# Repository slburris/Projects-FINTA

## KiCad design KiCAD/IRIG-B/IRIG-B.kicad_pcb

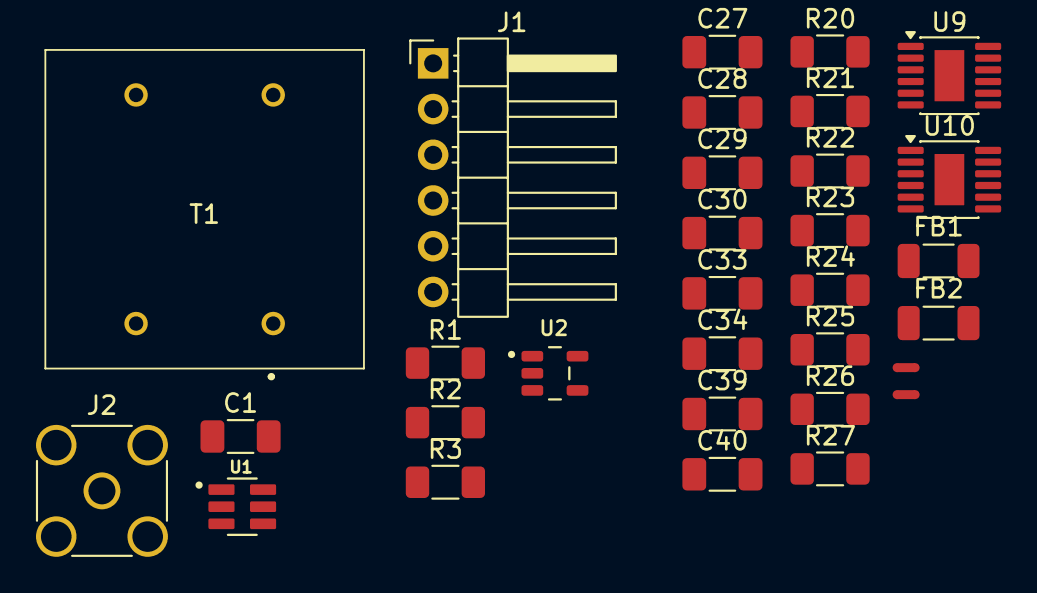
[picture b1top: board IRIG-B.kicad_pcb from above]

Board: 2 copper layers, 31 parts (0 on the bottom side), 26 nets, no tracks yet.

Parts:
C1, C27, C28, C30, C33, C34, C40: 10uf; C_1206_3216Metric_Pad1.33x1.80mm_HandSolder
C29, C39: 4.7uf; C_1206_3216Metric_Pad1.33x1.80mm_HandSolder
FB1, FB2: BLM31PG601; L_1206_3216Metric_Pad1.22x1.90mm_HandSolder
J1: Conn_01x06; PinHeader_1x06_P2.54mm_Horizontal
J2: Conn_Coaxial_Small; SMA_Amphenol_132291-12_Vertical
NT1, NT2: NetTie_2; NetTie-2_SMD_Pad0.5mm
R1: 1.4K; R_1206_3216Metric_Pad1.30x1.75mm_HandSolder
R2, R23: 1K; R_1206_3216Metric_Pad1.30x1.75mm_HandSolder
R3: 600; R_1206_3216Metric_Pad1.30x1.75mm_HandSolder
R20: 150K 0.1% 50ppm; R_1206_3216Metric_Pad1.30x1.75mm_HandSolder
R21, R25: 10K; R_1206_3216Metric_Pad1.30x1.75mm_HandSolder
R22: 113K; R_1206_3216Metric_Pad1.30x1.75mm_HandSolder
R24: 31.6K; R_1206_3216Metric_Pad1.30x1.75mm_HandSolder
R26: 50K 0.05% 5ppm; R_1206_3216Metric_Pad1.30x1.75mm_HandSolder
R27: 3K; R_1206_3216Metric_Pad1.30x1.75mm_HandSolder
T1: LM-NP-1001-B1L; LMNP1001B1L
U1: DAC121S101CIMKX_NOPB; SOT95P280X110-6N
U2: OPA171AIDBVR; SOT95P280X145-5NOPA171
U9, U10: LT3045xMSE; MSOP-12-1EP_3x4.039mm_P0.65mm_EP1.651x2.845mm

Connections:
+5VA: C40.1, NT2.2, U1.3 (VA), U9.11 (OUT), U9.12 (OUT)
+6V: C33.1, FB2.1
+15VA: C28.1, NT1.2, U2.5, U10.11 (OUT), U10.12 (OUT)
+16V: C30.1, FB1.1
GND: J1.2, R2.2, T1.4, U1.2 (GND), U2.2
GNDA: C27.2, C28.2, C29.2, C30.2, C33.2, C34.2, C39.2, C40.2, R20.2, R21.2, R23.2, R25.2, R26.2, R27.2, U9.9 (GND), U9.13 (GND), U10.9 (GND), U10.13 (GND)
unnamed: C1.1, R1.2, U2.1
unnamed: C1.2, R3.1
unnamed: J1.3, U1.5 (SCLK)
unnamed: J1.5, U1.4 (DIN)
unnamed: J1.6, U1.6 (~SYNC)
unnamed: J2.2 (Ext), T1.8
unnamed: J2.1 (In), T1.5
unnamed: R1.1, R2.1, U2.4
unnamed: R3.2, T1.1
unnamed: U1.1 (VOUT), U2.3
unnamed: R24.2, R25.1, U9.4 (EN/UV)
unnamed: R27.1, U9.6 (ILIM)
unnamed: NT2.1, U9.10 (OUTS)
unnamed: C34.1, FB2.2, R24.1, U9.1 (IN), U9.2 (IN), U9.3 (IN), U9.7 (PGFB)
unnamed: C39.1, R26.1, U9.8 (SET)
unnamed: R21.1, R22.2, U10.4 (EN/UV)
unnamed: R23.1, U10.6 (ILIM)
unnamed: NT1.1, U10.10 (OUTS)
unnamed: C27.1, FB1.2, R22.1, U10.1 (IN), U10.2 (IN), U10.3 (IN), U10.7 (PGFB)
unnamed: C29.1, R20.1, U10.8 (SET)

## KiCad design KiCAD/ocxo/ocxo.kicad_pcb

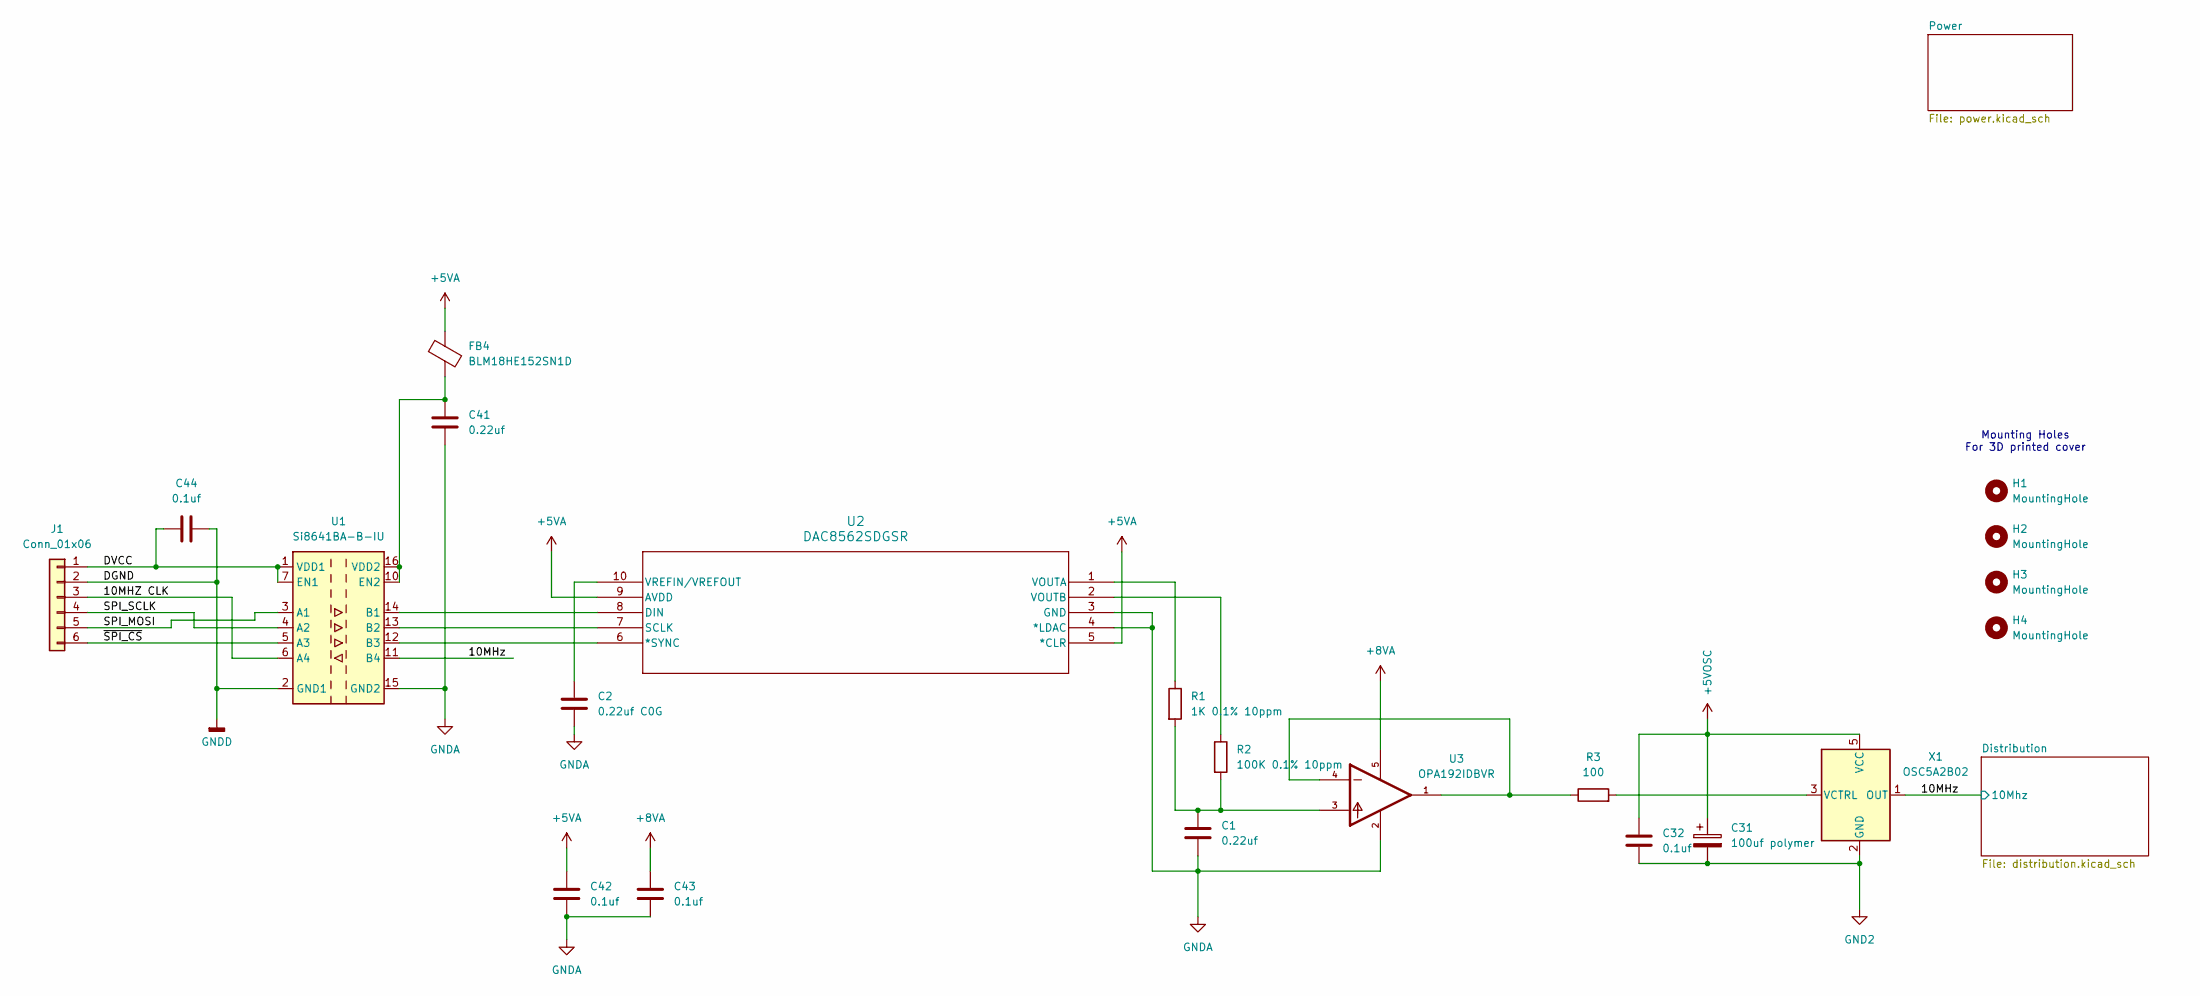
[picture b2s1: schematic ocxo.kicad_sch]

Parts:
C1, C41: 0.22uf; C_1206_3216Metric_Pad1.33x1.80mm_HandSolder
C2: 0.22uf C0G; C_1206_3216Metric_Pad1.33x1.80mm_HandSolder
C31: 100uf polymer; CP_Radial_D5.0mm_P2.00mm
C32, C42, C43, C44: 0.1uf; C_1206_3216Metric_Pad1.33x1.80mm_HandSolder
FB4: BLM18HE152SN1D; L_0603_1608Metric_Pad1.05x0.95mm_HandSolder
H1, H2, H3, H4: MountingHole; MountingHole_3.2mm_M3
J1: Conn_01x06; PinHeader_1x06_P2.54mm_Horizontal
R1: 1K 0.1% 10ppm; R_0603_1608Metric_Pad0.98x0.95mm_HandSolder
R2: 100K 0.1% 10ppm; R_0603_1608Metric_Pad0.98x0.95mm_HandSolder
R3: 100; R_1206_3216Metric_Pad1.30x1.75mm_HandSolder
U1: Si8641BA-B-IU; QSOP-16_3.9x4.9mm_P0.635mm
U2: DAC8562SDGSR; DGS10
U3: OPA192IDBVR; SOT95P280X145-5N; PARTREV F
X1: OSC5A2B02; CTI-OSC-25x25

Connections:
+5VA: C42.1, FB4.1, U2.5 (*CLR), U2.9 (AVDD); also elsewhere on the board
+5VOSC: C31.1, C32.1, X1.5 (VCC); also elsewhere on the board
+8VA: C43.1, U3.5; also elsewhere on the board
/10MHZ CLK: J1.3, U1.6 (A4)
/10MHz: U1.11 (B4), X1.1 (OUT); also elsewhere on the board
/DVCC: C44.1, J1.1, U1.1 (VDD1), U1.7 (EN1)
/SPI_MOSI: J1.5, U1.3 (A1)
/SPI_SCLK: J1.4, U1.4 (A2)
/~SPI_CS: J1.6, U1.5 (A3)
GND2: C31.2, C32.2, X1.2 (GND); also elsewhere on the board
GNDA: C1.2, C2.2, C41.2, C42.2, C43.2, U1.9 (GND2), U1.15 (GND2), U2.3 (GND), U2.4 (*LDAC), U3.2; also elsewhere on the board
GNDD: C44.2, J1.2, U1.2 (GND1), U1.8 (GND1)
unnamed: C1.1, R1.2, R2.2, U3.3
unnamed: R3.1, U3.1, U3.4
unnamed: U1.14 (B1), U2.8 (DIN)
unnamed: U1.13 (B2), U2.7 (SCLK)
unnamed: U1.12 (B3), U2.6 (*SYNC)
unnamed: C41.1, FB4.2, U1.10 (EN2), U1.16 (VDD2)
unnamed: R1.1, U2.1 (VOUTA)
unnamed: R2.1, U2.2 (VOUTB)
unnamed: C2.1, U2.10 (VREFIN/VREFOUT)
unnamed: R3.2, X1.3 (VCTRL)

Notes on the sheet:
Mounting Holes For 3D printed cover

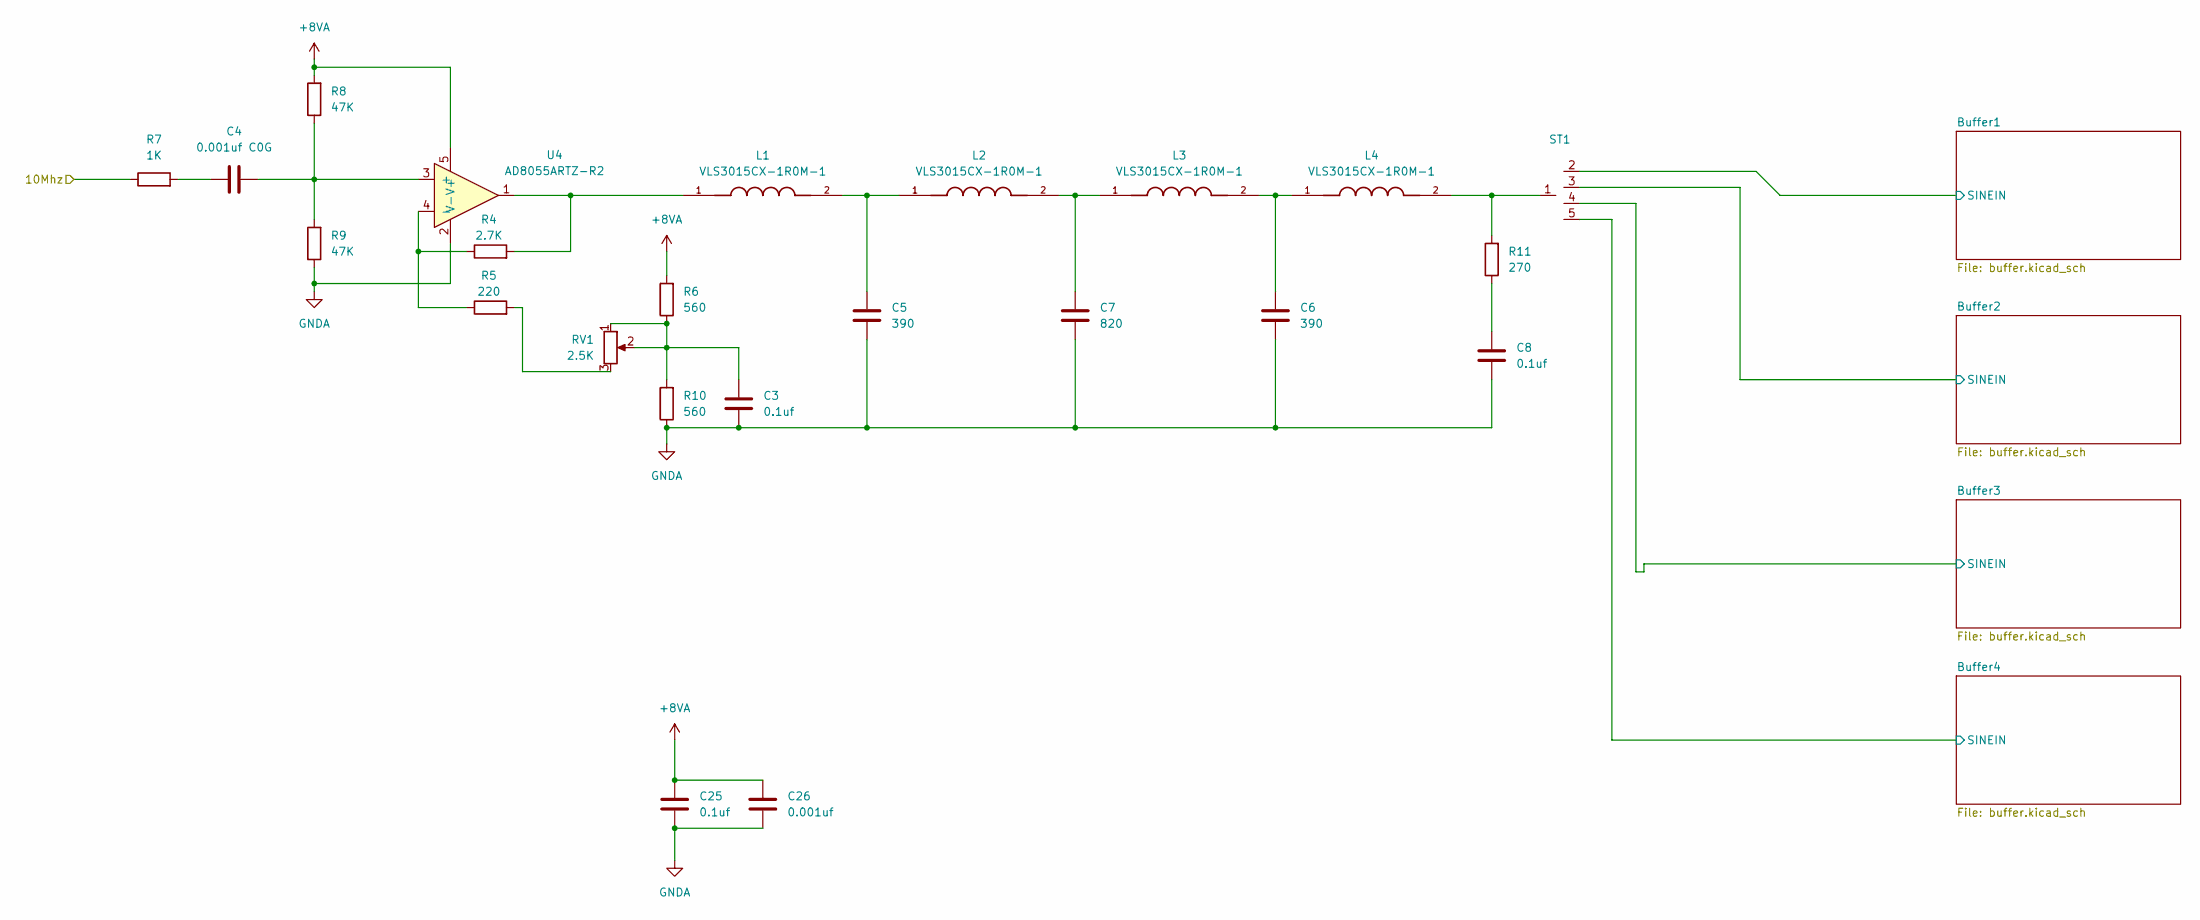
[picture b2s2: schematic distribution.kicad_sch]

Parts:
C3, C8, C25: 0.1uf; C_1206_3216Metric_Pad1.33x1.80mm_HandSolder
C4: 0.001uf C0G; C_1206_3216Metric_Pad1.33x1.80mm_HandSolder
C5, C6: 390; C_1206_3216Metric_Pad1.33x1.80mm_HandSolder
C7: 820; C_1206_3216Metric_Pad1.33x1.80mm_HandSolder
C26: 0.001uf; C_1206_3216Metric_Pad1.33x1.80mm_HandSolder
L1, L2, L3, L4: VLS3015CX-1R0M-1; IND_VLS3015CX-1R0M-1; PARTREV N/A
R4: 2.7K; R_1206_3216Metric_Pad1.30x1.75mm_HandSolder
R5: 220; R_1206_3216Metric_Pad1.30x1.75mm_HandSolder
R6, R10: 560; R_1206_3216Metric_Pad1.30x1.75mm_HandSolder
R7: 1K; R_1206_3216Metric_Pad1.30x1.75mm_HandSolder
R8, R9: 47K; R_1206_3216Metric_Pad1.30x1.75mm_HandSolder
R11: 270; R_1206_3216Metric_Pad1.30x1.75mm_HandSolder
RV1: 2.5K; Potentiometer_Bourns_3296W_Vertical
ST1: star5tie
U4: AD8055ARTZ-R2; SOT95P290X145-5N; MPN AD8055ARTZ-R2

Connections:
+8VA: C25.1, C26.1, R6.2, R8.2, U4.5 (V+); also elsewhere on the board
/10MHz: R7.1; also elsewhere on the board
/Distribution/Buffer1/SINEIN: ST1.2; also elsewhere on the board
/Distribution/Buffer2/SINEIN: ST1.3; also elsewhere on the board
/Distribution/Buffer3/SINEIN: ST1.4; also elsewhere on the board
/Distribution/Buffer4/SINEIN: ST1.5; also elsewhere on the board
GNDA: C3.2, C5.2, C6.2, C7.2, C8.2, C25.2, C26.2, R9.1, R10.1, U4.2 (V-); also elsewhere on the board
unnamed: C3.1, R6.1, R10.2, RV1.1, RV1.2
unnamed: C4.1, R7.2
unnamed: C5.1, L1.2, L2.1
unnamed: C6.1, L3.2, L4.1
unnamed: C7.1, L2.2, L3.1
unnamed: C8.1, R11.1
unnamed: L1.1, R4.2, U4.1
unnamed: L4.2, R11.2, ST1.1
unnamed: R5.2, RV1.3
unnamed: C4.2, R8.1, R9.2, U4.3 (+)
unnamed: R4.1, R5.1, U4.4 (-)

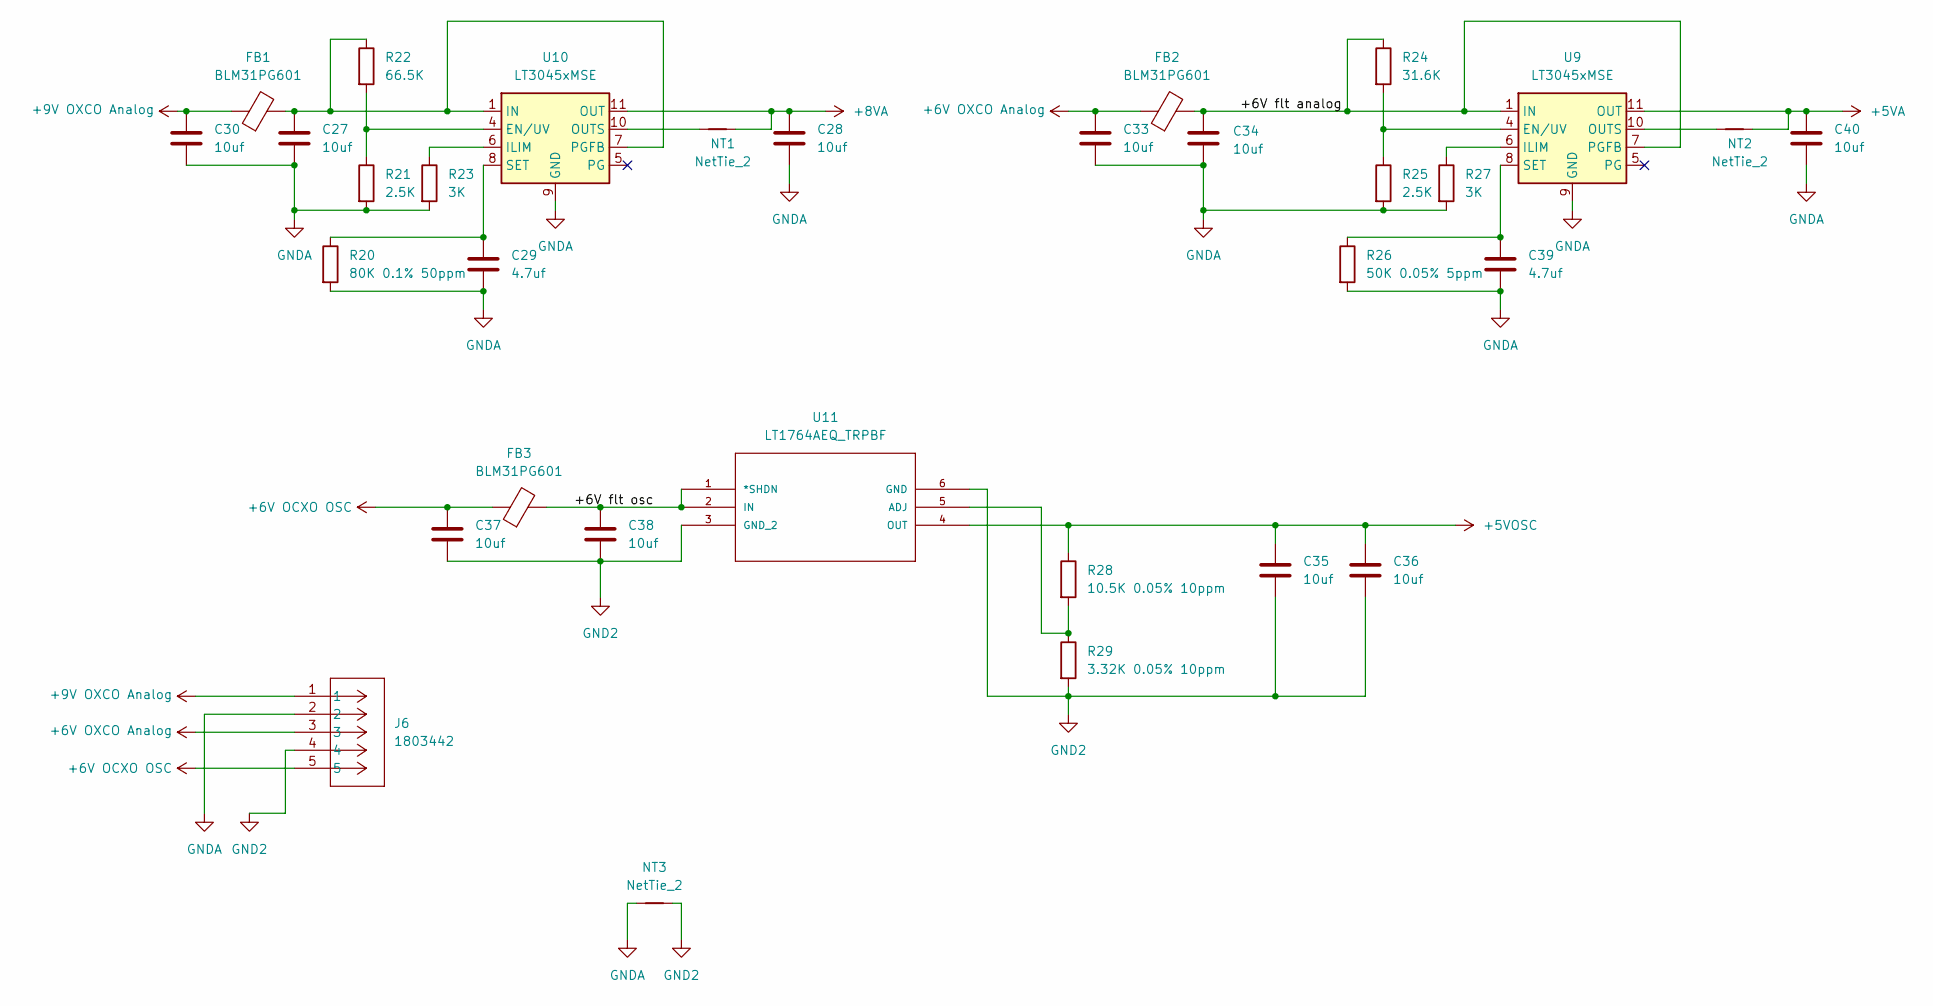
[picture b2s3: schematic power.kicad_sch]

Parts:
C27, C28, C30, C33, C34, C35, C36, C37, C38, C40: 10uf; C_1206_3216Metric_Pad1.33x1.80mm_HandSolder
C29, C39: 4.7uf; C_1206_3216Metric_Pad1.33x1.80mm_HandSolder
FB1, FB2, FB3: BLM31PG601; L_1206_3216Metric_Pad1.22x1.90mm_HandSolder
J6: 1803442; CONN_1803455; PARTREV 25.02.2015
NT1, NT2: NetTie_2; NetTie-2_SMD_Pad0.5mm
NT3: NetTie_2; NetTie-2_SMD_Pad2.0mm
R20: 80K 0.1% 50ppm; R_1206_3216Metric_Pad1.30x1.75mm_HandSolder
R21, R25: 2.5K; R_0603_1608Metric_Pad0.98x0.95mm_HandSolder
R22: 66.5K; R_0603_1608Metric_Pad0.98x0.95mm_HandSolder
R23, R27: 3K; R_1206_3216Metric_Pad1.30x1.75mm_HandSolder
R24: 31.6K; R_0603_1608Metric_Pad0.98x0.95mm_HandSolder
R26: 50K 0.05% 5ppm; R_1206_3216Metric_Pad1.30x1.75mm_HandSolder
R28: 10.5K 0.05% 10ppm; R_1206_3216Metric_Pad1.30x1.75mm_HandSolder
R29: 3.32K 0.05% 10ppm; R_1206_3216Metric_Pad1.30x1.75mm_HandSolder
U9, U10: LT3045xMSE; MSOP-12-1EP_3x4.039mm_P0.65mm_EP1.651x2.845mm
U11: LT1764AEQ_TRPBF; DDPAK-5_Q; MANUFACTURER_PART_NUMBER LT1764AEQ#TRPBF; DIGIKEY_PART_NUMBER LT1764AEQ#TRPBFND

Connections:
+5VA: C40.1, NT2.2, U9.11 (OUT), U9.12 (OUT); also elsewhere on the board
+5VOSC: C35.1, C36.1, R28.1, U11.4 (OUT); also elsewhere on the board
+6V OCXO OSC: C37.1, FB3.1, J6.5
+6V OXCO Analog: C33.1, FB2.1, J6.3
+8VA: C28.1, NT1.2, U10.11 (OUT), U10.12 (OUT); also elsewhere on the board
+9V OXCO Analog: C30.1, FB1.1, J6.1
/Power/+6V flt analog: C34.1, FB2.2, R24.1, U9.1 (IN), U9.2 (IN), U9.3 (IN), U9.7 (PGFB)
/Power/+6V flt osc: C38.1, FB3.2, U11.1 (*SHDN), U11.2 (IN)
GND2: C35.2, C36.2, C37.2, C38.2, J6.4, NT3.2, R29.2, U11.3 (GND_2), U11.6 (GND); also elsewhere on the board
GNDA: C27.2, C28.2, C29.2, C30.2, C33.2, C34.2, C39.2, C40.2, J6.2, NT3.1, R20.2, R21.2, R23.2, R25.2, R26.2, R27.2, U9.9 (GND), U9.13 (GND), U10.9 (GND), U10.13 (GND); also elsewhere on the board
unnamed: R24.2, R25.1, U9.4 (EN/UV)
unnamed: R27.1, U9.6 (ILIM)
unnamed: NT2.1, U9.10 (OUTS)
unnamed: C39.1, R26.1, U9.8 (SET)
unnamed: R21.1, R22.2, U10.4 (EN/UV)
unnamed: R23.1, U10.6 (ILIM)
unnamed: NT1.1, U10.10 (OUTS)
unnamed: C27.1, FB1.2, R22.1, U10.1 (IN), U10.2 (IN), U10.3 (IN), U10.7 (PGFB)
unnamed: C29.1, R20.1, U10.8 (SET)
unnamed: R28.2, R29.1, U11.5 (ADJ)

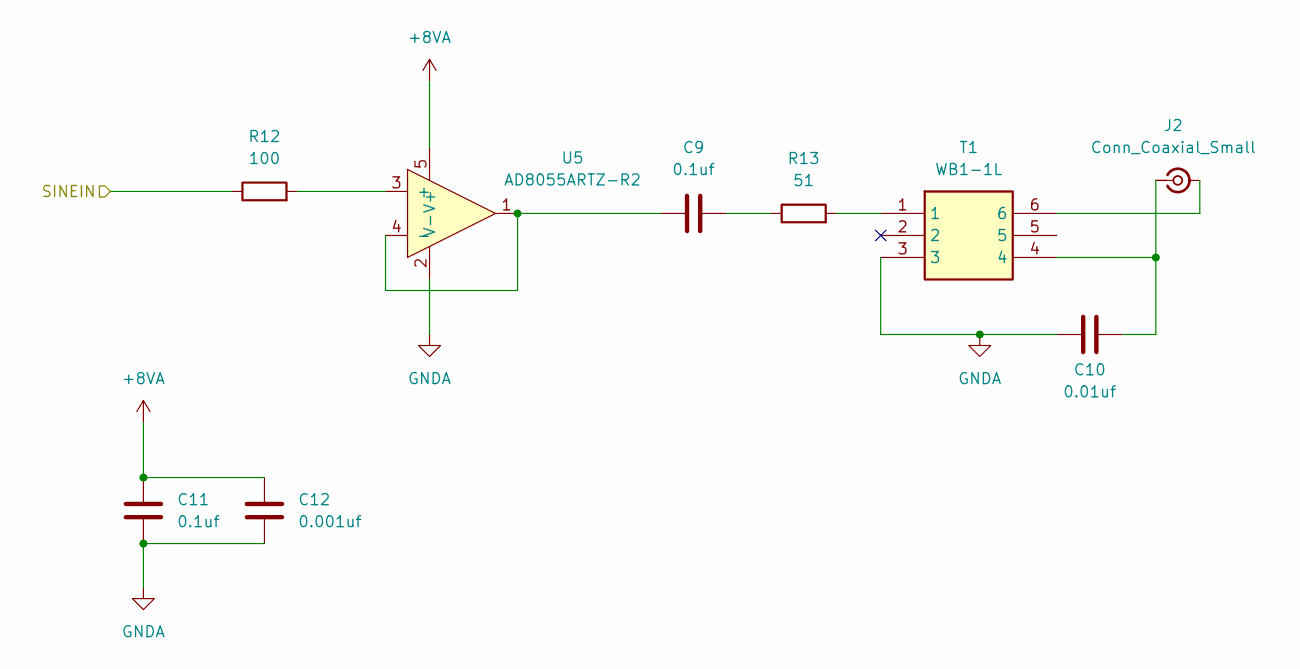
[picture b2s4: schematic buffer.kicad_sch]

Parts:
C9, C11: 0.1uf; C_1206_3216Metric_Pad1.33x1.80mm_HandSolder
C10: 0.01uf; C_1206_3216Metric_Pad1.33x1.80mm_HandSolder
C12: 0.001uf; C_1206_3216Metric_Pad1.33x1.80mm_HandSolder
J2: Conn_Coaxial_Small; SMA_Amphenol_132291-12_Vertical
R12: 100; R_1206_3216Metric_Pad1.30x1.75mm_HandSolder
R13: 51; R_1206_3216Metric_Pad1.30x1.75mm_HandSolder
T1: WB1-1L; DIP762W64P254L826H572Q6N; Manufacturer_Part_Number WB1-1L; Mouser Part Number 994-WB1-1L
U5: AD8055ARTZ-R2; SOT95P290X145-5N; MPN AD8055ARTZ-R2

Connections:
+8VA: C11.1, C12.1, U5.5 (V+); also elsewhere on the board
/Distribution/Buffer1/SINEIN: R12.1; also elsewhere on the board
GNDA: C10.1, C11.2, C12.2, T1.3, U5.2 (V-); also elsewhere on the board
unnamed: C9.2, R13.1
unnamed: J2.2 (Ext), T1.6
unnamed: C10.2, J2.1 (In), T1.4
unnamed: R13.2, T1.1
unnamed: R12.2, U5.3 (+)
unnamed: C9.1, U5.1, U5.4 (-)

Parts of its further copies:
C13, C15, C17, C19, C21, C23: 0.1uf; C_1206_3216Metric_Pad1.33x1.80mm_HandSolder
C14, C18, C22: 0.001uf; C_1206_3216Metric_Pad1.33x1.80mm_HandSolder
C16, C20, C24: 0.01uf; C_1206_3216Metric_Pad1.33x1.80mm_HandSolder
J3, J4, J5: Conn_Coaxial_Small; SMA_Amphenol_132291-12_Vertical
R14, R16, R18: 100; R_1206_3216Metric_Pad1.30x1.75mm_HandSolder
R15, R17, R19: 51; R_1206_3216Metric_Pad1.30x1.75mm_HandSolder
T2, T3, T4: WB1-1L; DIP762W64P254L826H572Q6N; Manufacturer_Part_Number WB1-1L; Mouser Part Number 994-WB1-1L
U6, U7, U8: AD8055ARTZ-R2; SOT95P290X145-5N; MPN AD8055ARTZ-R2

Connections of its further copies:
+8VA: C13.1, C14.1, C17.1, C18.1, C21.1, C22.1, U6.5 (V+), U7.5 (V+), U8.5 (V+); also elsewhere on the board
/Distribution/Buffer2/SINEIN: R14.1; also elsewhere on the board
/Distribution/Buffer3/SINEIN: R16.1; also elsewhere on the board
/Distribution/Buffer4/SINEIN: R18.1; also elsewhere on the board
GNDA: C13.2, C14.2, C16.1, C17.2, C18.2, C20.1, C21.2, C22.2, C24.1, T2.3, T3.3, T4.3, U6.2 (V-), U7.2 (V-), U8.2 (V-); also elsewhere on the board
unnamed: C15.2, R15.1
unnamed: C19.2, R17.1
unnamed: C23.2, R19.1
unnamed: J3.2 (Ext), T2.6
unnamed: C16.2, J3.1 (In), T2.4
unnamed: J4.2 (Ext), T3.6
unnamed: C20.2, J4.1 (In), T3.4
unnamed: J5.2 (Ext), T4.6
unnamed: C24.2, J5.1 (In), T4.4
unnamed: R15.2, T2.1
unnamed: R17.2, T3.1
unnamed: R19.2, T4.1
unnamed: R14.2, U6.3 (+)
unnamed: C15.1, U6.1, U6.4 (-)
unnamed: R16.2, U7.3 (+)
unnamed: C19.1, U7.1, U7.4 (-)
unnamed: R18.2, U8.3 (+)
unnamed: C23.1, U8.1, U8.4 (-)

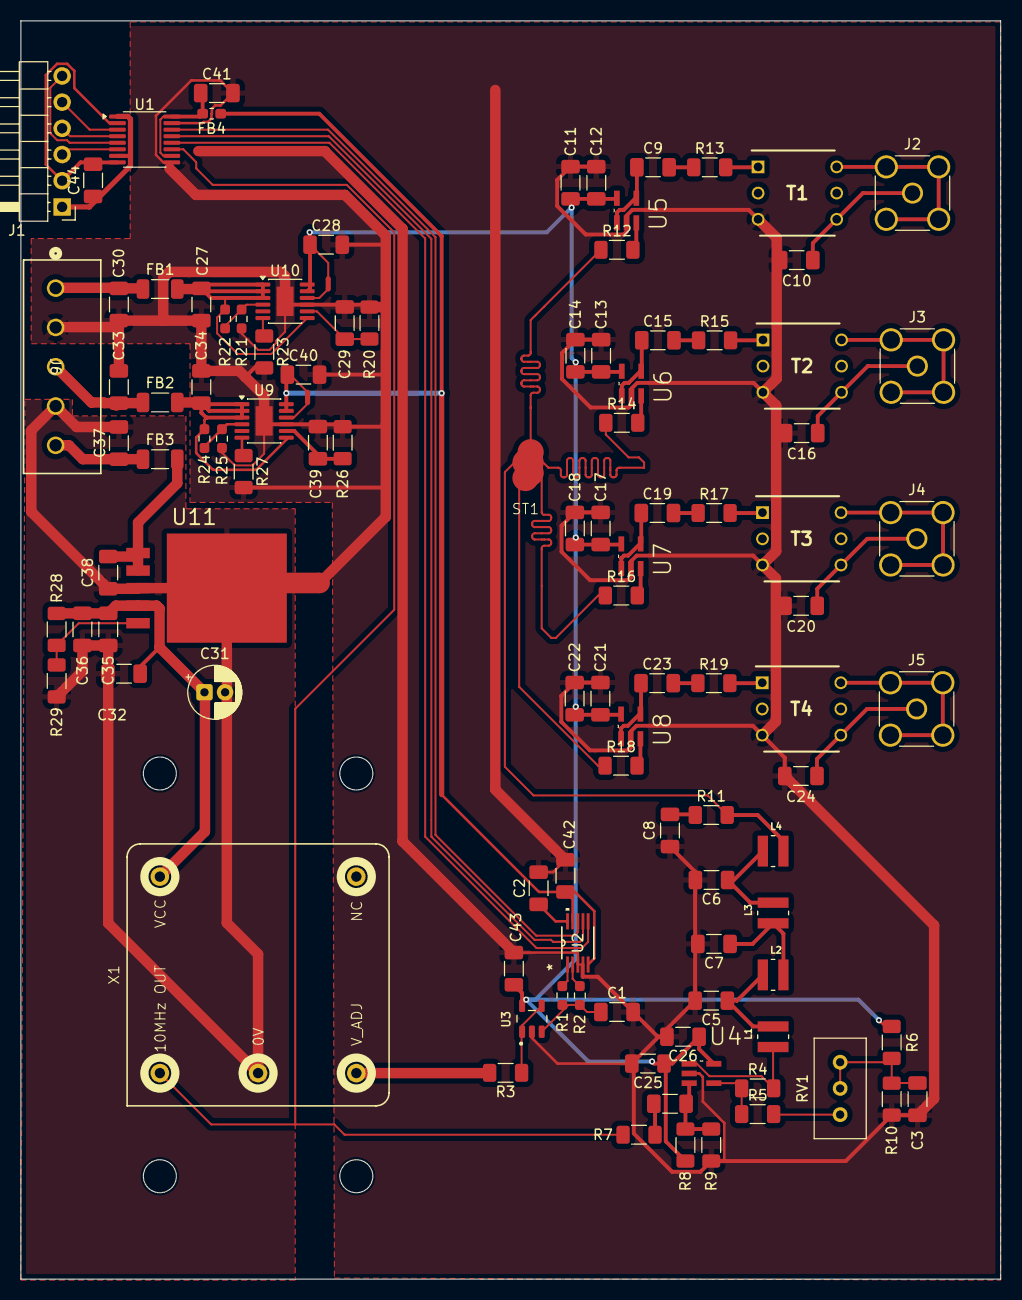
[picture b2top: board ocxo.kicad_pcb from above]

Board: 2 copper layers, 95.0 x 122.0 mm, 112 parts (0 on the bottom side), 76 nets.

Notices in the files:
parts and their libraries:
COPYRIGHT: Copyright C 2016 Accelerated Designs. All rights reserved
